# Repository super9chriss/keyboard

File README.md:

# custom keyboard
This is a split keyboard which can be aligned to work like a normal keyboard, it also has a removable numpad which conects to the main keyboard using pogo connectors. 
The keycaps are going to be 3d printed using these keycaps: https://www.printables.com/model/593307-low-profile-small-mx-keycaps-set/files

I wanted to make a split keyboard since my wrist hurt after typing for a long time, but im used to typing on a normal keyboard so i wanted to have this possiblity aswel,
i use a numpad for some programs so i also wanted to have that but since my desk is alway cluttered with stuff i wanted to have a keyboard which isnt too big so i made it removable.
## PCB and schematic
| **PCB Layout** | **Schematic** |
| :---: | :---: |
||
||
||
|| 
## BOM
|Description        |quantity              |price                 |link                                                                                                                                                                                                                                                                                  |
|-------------------|----------------------|----------------------|--------------------------------------------------------------------------------------------------------------------------------------------------------------------------------------------------------------------------------------------------------------------------------------|
|switches           |110                   |25.99 + 4.72(shipping)|https://nl.aliexpress.com/item/1005010167220637.html?spm=a2g0o.cart.0.0.14d561d7dqnSf7&mp=1&pdp_npi=6%40dis%21EUR%21EUR%2046.41%21EUR%2025.99%21%21EUR%2023.51%21%21%21%40211b813b17699617589272174ea3c6%2112000051388572877%21ct%21NL%217243002615%21%211%210%21&gatewayAdapt=glo2nld|
|Pico               |2                     |4.89                  |https://nl.aliexpress.com/item/1005006839247100.html?spm=a2g0o.cart.0.0.14d561d7dqnSf7&mp=1&pdp_npi=6%40dis%21EUR%21EUR%204.89%21EUR%204.89%21%21EUR%204.42%21%21%21%40211b813b17699617589272174ea3c6%2112000051567246192%21ct%21NL%217243002615%21%211%210%21&gatewayAdapt=glo2nld   |
|pogo connector 5pin|2                     |7.02                  |https://nl.aliexpress.com/item/1005006839247100.html?spm=a2g0o.cart.0.0.14d561d7dqnSf7&mp=1&pdp_npi=6%40dis%21EUR%21EUR%204.89%21EUR%204.89%21%21EUR%204.42%21%21%21%40211b813b17699617589272174ea3c6%2112000051567246192%21ct%21NL%217243002615%21%211%210%21&gatewayAdapt=glo2nld   |
|diodes             |110(need to order 200)|3.98                  |https://nl.aliexpress.com/item/1005005574663623.html?spm=a2g0o.cart.0.0.14d561d7dqnSf7&mp=1&pdp_npi=6%40dis%21EUR%21EUR%201.99%21EUR%201.99%21%21EUR%201.80%21%21%21%40211b813b17699617589272174ea3c6%2112000033607802196%21ct%21NL%217243002615%21%212%210%21&gatewayAdapt=glo2nld   |
|PCB                |1                     |41.14                 |https://cart.jlcpcb.com/shopcart/cart                                                                                                                                                                                                                                                 |
|LED               |1                     |0              |Self sourced                                                                                                                                                                                                                                               |
|                   |total in euro:        |87.74                 |aliexpress coupon saves 4 euro so 83.74                                                                                                                                                                                                                                               |
|                   |in usd                |100                   |                                                                                                                                                                                                                                                                                      |

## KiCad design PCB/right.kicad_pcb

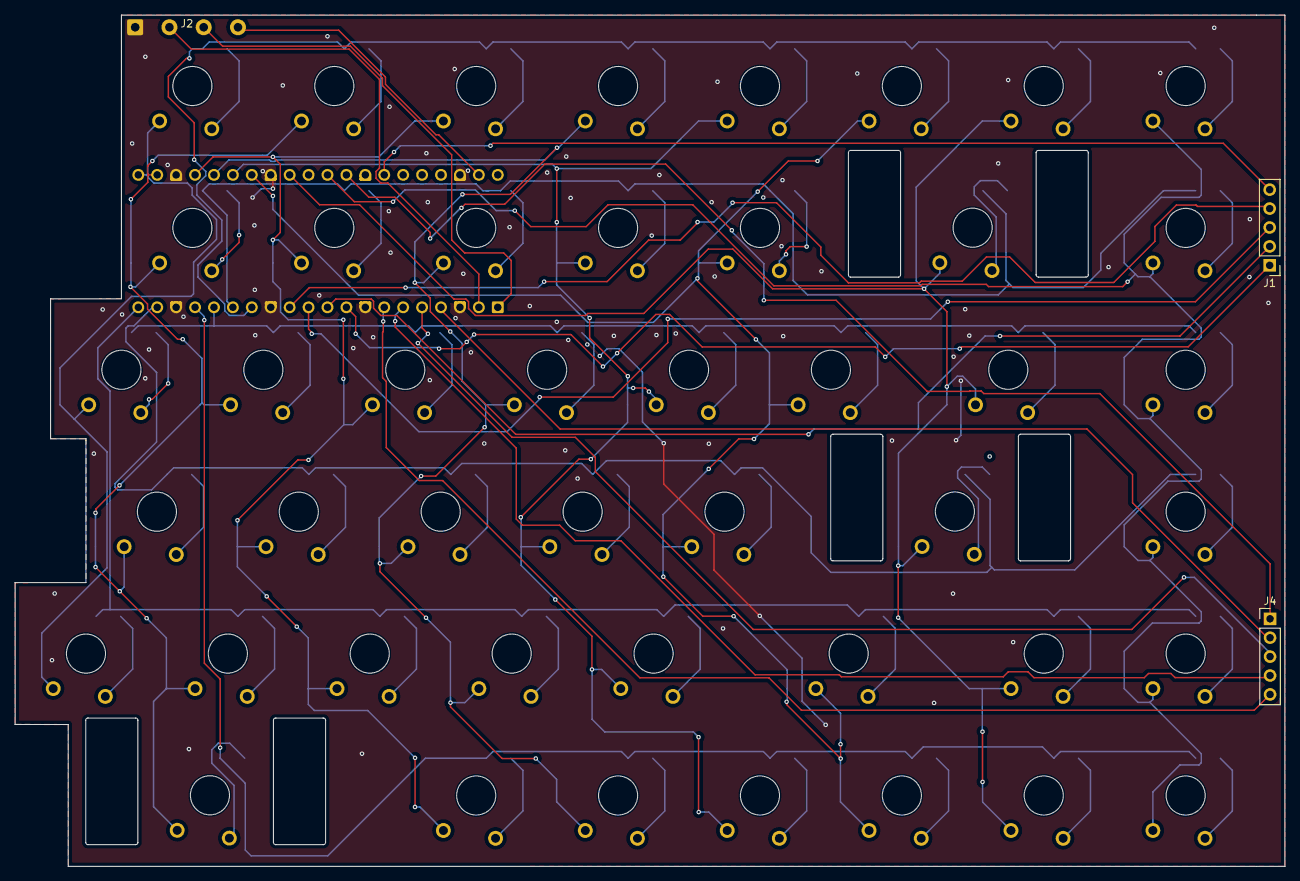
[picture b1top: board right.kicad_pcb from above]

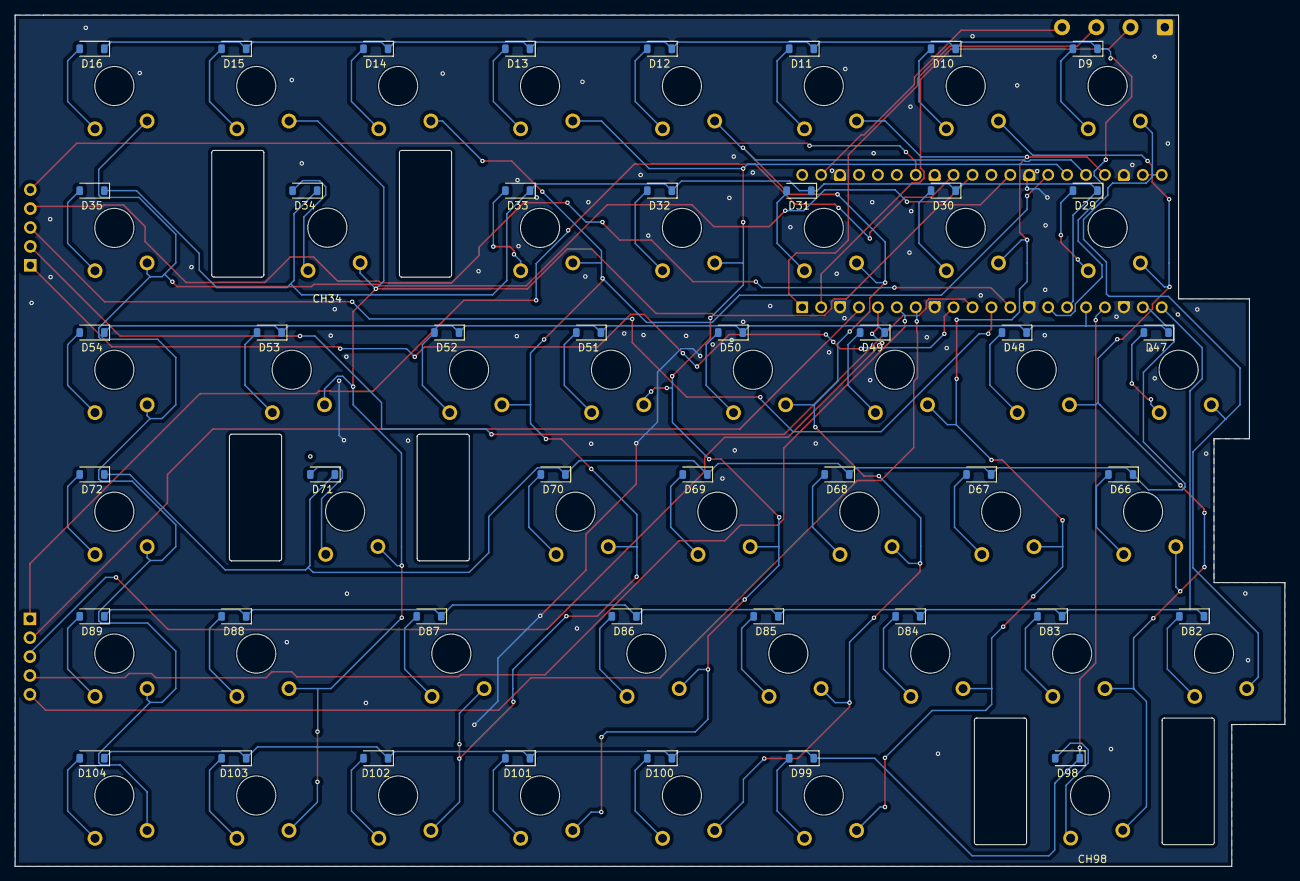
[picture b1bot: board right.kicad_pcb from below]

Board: 2 copper layers, 170.5 x 114.3 mm, 94 parts (46 on the bottom side), 73 nets.

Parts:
A1: RaspberryPi_Pico; RaspberryPi_Pico_Common_THT no silk only pins
CH9, CH10, CH11, CH12, CH13, CH14, CH15, CH16, CH29, CH30, CH31, CH32, CH33, CH35, CH47, CH48, CH49, CH50, CH51, CH52, CH53, CH54, CH66, CH67, CH68, CH69, CH70, CH72, CH82, CH83, CH84, CH85, CH86, CH87, CH88, CH89, CH99, CH100, CH101, CH102, CH103, CH104: KS33_SW_HS; SW_KS33_1u
CH34, CH71, CH98: KS33_SW_HS; Gateron_Low_Profile_Socket_Stabilizer_2U
D9, D10, D11, D12, D13, D14, D15, D16, D29, D30, D31, D32, D33, D34, D35, D47, D48, D49, D50, D51, D52, D53, D54, D66, D67, D68, D69, D70, D71, D72, D82, D83, D84, D85, D86, D87, D88, D89, D98, D99, D100, D101, D102, D103, D104: D; D_SOD-123
J1, J4: Conn_01x05_Socket; PinHeader_1x05_P2.54mm_Vertical
J2: Conn_01x04_Socket; SolderWire-0.5sqmm_1x04_P4.6mm_D0.9mm_OD2.1mm

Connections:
GND1: A1.3 (GND), A1.8 (GND), A1.13 (GND), A1.18 (GND), A1.23 (GND), A1.28 (GND), A1.38 (GND), J2.1
unnamed: A1.1 (GPIO0), J2.3
unnamed: A1.2 (GPIO1), J2.2
unnamed: A1.39 (VSYS), J2.4
unnamed: CH9.2, D9.2 (A)
unnamed: CH10.2, D10.2 (A)
unnamed: CH11.2, D11.2 (A)
unnamed: CH12.2, D12.2 (A)
unnamed: CH13.2, D13.2 (A)
unnamed: CH14.2, D14.2 (A)
unnamed: CH15.2, D15.2 (A)
unnamed: CH16.2, D16.2 (A)
unnamed: CH29.2, D29.2 (A)
unnamed: CH30.2, D30.2 (A)
unnamed: CH31.2, D31.2 (A)
unnamed: CH32.2, D32.2 (A)
unnamed: CH33.2, D33.2 (A)
unnamed: CH34.2, D34.2 (A)
unnamed: CH35.2, D35.2 (A)
unnamed: CH47.2, D47.2 (A)
unnamed: CH48.2, D48.2 (A)
unnamed: CH49.2, D49.2 (A)
unnamed: CH50.2, D50.2 (A)
unnamed: CH51.2, D51.2 (A)
unnamed: CH52.2, D52.2 (A)
unnamed: CH53.2, D53.2 (A)
unnamed: CH54.2, D54.2 (A)
unnamed: CH66.2, D66.2 (A)
unnamed: CH67.2, D67.2 (A)
unnamed: CH68.2, D68.2 (A)
unnamed: CH69.2, D69.2 (A)
unnamed: CH70.2, D70.2 (A)
unnamed: CH71.2, D71.2 (A)
unnamed: CH72.2, D72.2 (A)
unnamed: CH82.2, D82.2 (A)
unnamed: CH83.2, D83.2 (A)
unnamed: CH84.2, D84.2 (A)
unnamed: CH85.2, D85.2 (A)
unnamed: CH86.2, D86.2 (A)
unnamed: CH87.2, D87.2 (A)
unnamed: CH88.2, D88.2 (A)
unnamed: CH89.2, D89.2 (A)
unnamed: CH98.2, D98.2 (A)
unnamed: CH99.2, D99.2 (A)
unnamed: CH100.2, D100.2 (A)
unnamed: CH101.2, D101.2 (A)
unnamed: CH102.2, D102.2 (A)
unnamed: CH103.2, D103.2 (A)
unnamed: CH104.2, D104.2 (A)
col8: A1.21 (GPIO16), CH9.1, CH47.1, CH82.1
col9: A1.22 (GPIO17), CH10.1, CH29.1, CH48.1, CH66.1, CH83.1, CH98.1
col10: A1.24 (GPIO18), CH11.1, CH30.1, CH49.1, CH67.1, CH84.1, CH99.1
col11: A1.25 (GPIO19), CH12.1, CH31.1, CH50.1, CH68.1, CH85.1, CH100.1
col12: A1.26 (GPIO20), CH13.1, CH32.1, CH51.1, CH69.1, CH86.1, CH101.1
col13: A1.27 (GPIO21), CH14.1, CH33.1, CH52.1, CH70.1, CH87.1, CH102.1
col14: A1.29 (GPIO22), CH15.1, CH34.1, CH53.1, CH71.1, CH88.1, CH103.1
col15: A1.31 (GPIO26_ADC0), CH16.1, CH35.1, CH54.1, CH72.1, CH89.1, CH104.1
col16: A1.12 (GPIO9), J1.4
col17: A1.11 (GPIO8), J1.3
col18: A1.10 (GPIO7), J1.2
col19: A1.9 (GPIO6), J1.1
row6: A1.14 (GPIO10), D9.1 (K), D10.1 (K), D11.1 (K), D12.1 (K), D13.1 (K), D14.1 (K), D15.1 (K), D16.1 (K)
row7: A1.15 (GPIO11), D29.1 (K), D30.1 (K), D31.1 (K), D32.1 (K), D33.1 (K), D34.1 (K), D35.1 (K)
row8: A1.16 (GPIO12), D47.1 (K), D48.1 (K), D49.1 (K), D50.1 (K), D51.1 (K), D52.1 (K), D53.1 (K), D54.1 (K)
row9: A1.19 (GPIO14), D66.1 (K), D67.1 (K), D68.1 (K), D69.1 (K), D70.1 (K), D71.1 (K), D72.1 (K)
row10: A1.20 (GPIO15), D82.1 (K), D83.1 (K), D84.1 (K), D85.1 (K), D86.1 (K), D87.1 (K), D88.1 (K), D89.1 (K)
row11: A1.17 (GPIO13), D98.1 (K), D99.1 (K), D100.1 (K), D101.1 (K), D102.1 (K), D103.1 (K), D104.1 (K)
row12: A1.34 (GPIO28_ADC2), J1.5
row13: A1.32 (GPIO27_ADC1), J4.1
row14: A1.4 (GPIO2), J4.2
row15: A1.5 (GPIO3), J4.3
row16: A1.6 (GPIO4), J4.4
row17: A1.7 (GPIO5), J4.5

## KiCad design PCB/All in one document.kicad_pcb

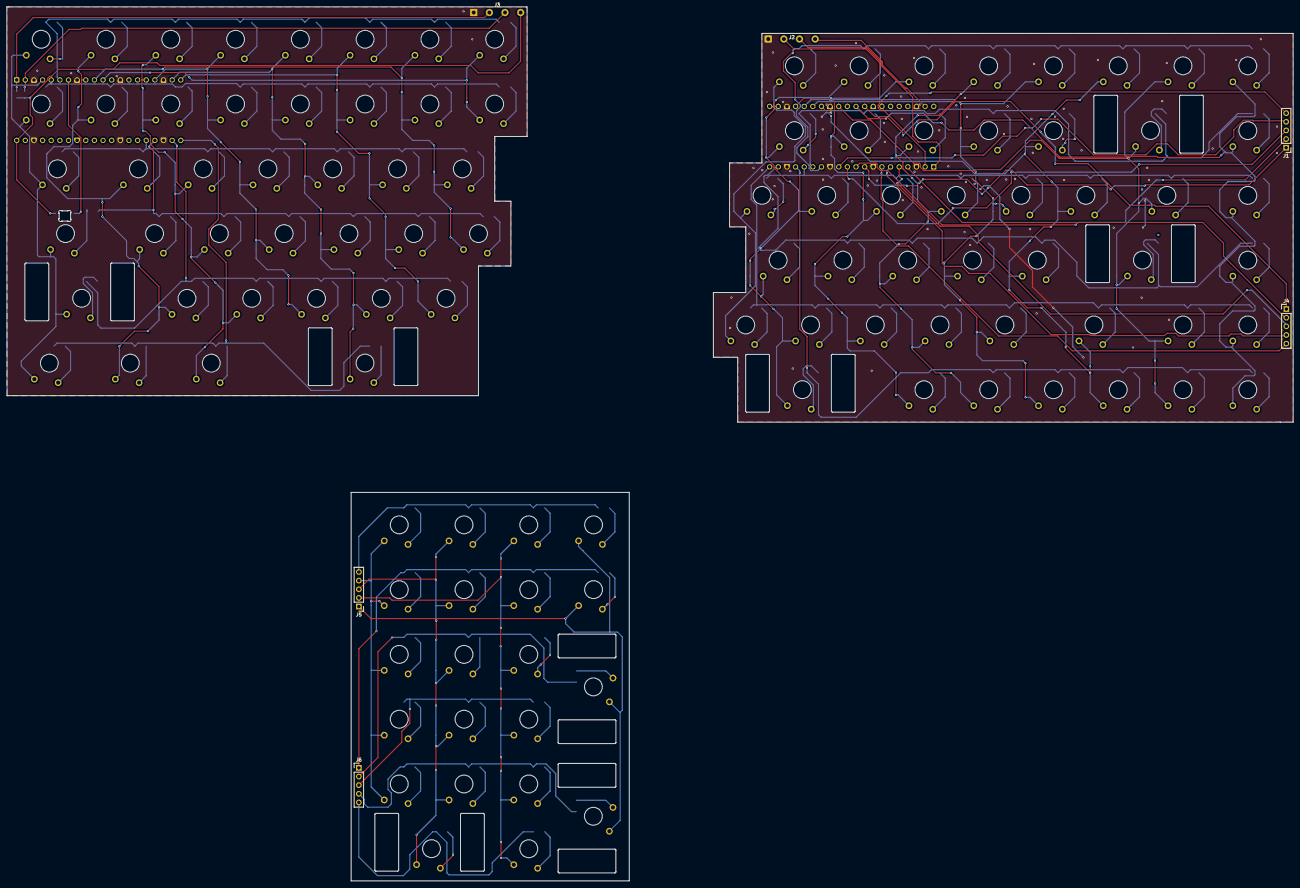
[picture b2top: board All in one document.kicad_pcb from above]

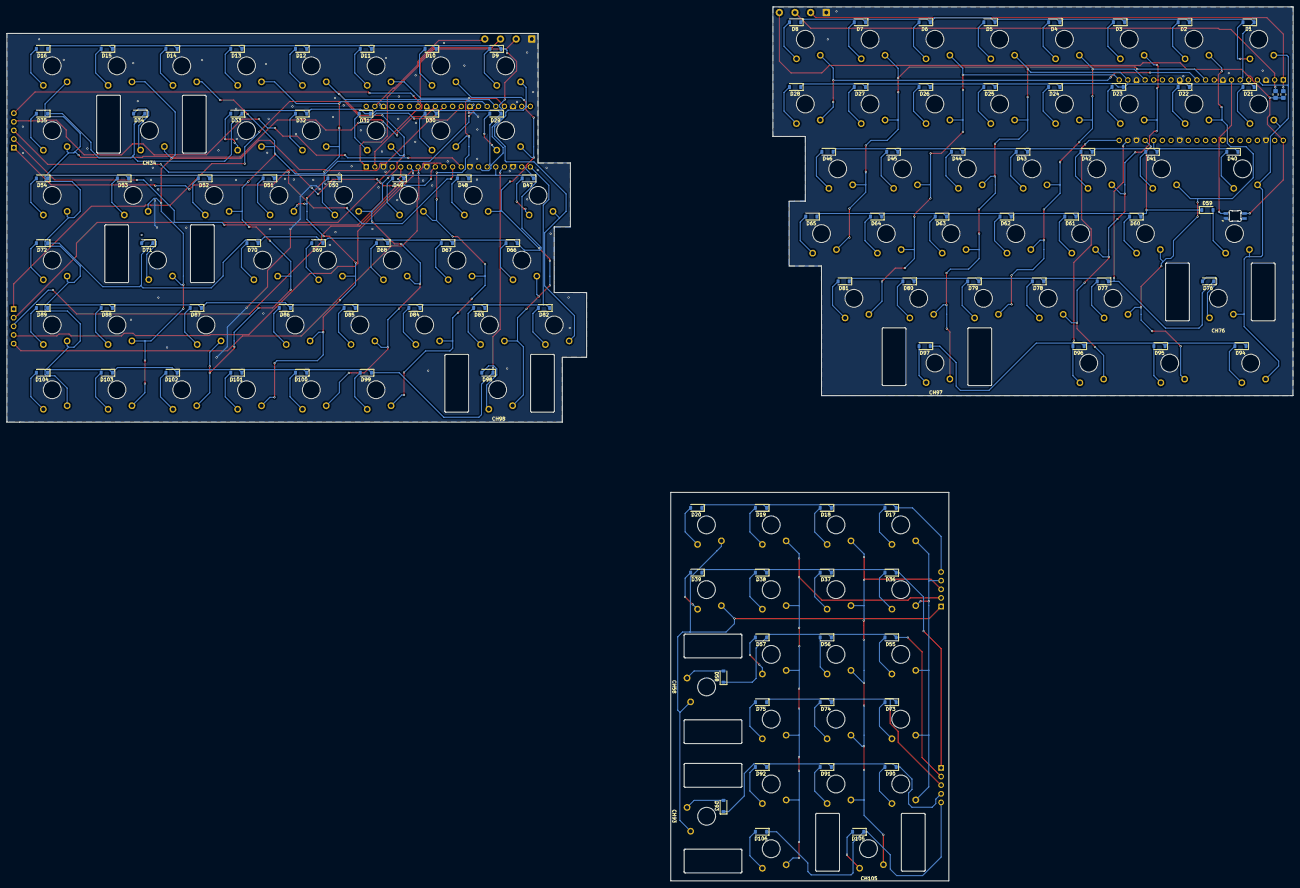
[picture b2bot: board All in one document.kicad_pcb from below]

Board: 2 copper layers, 378.3 x 257.0 mm, 223 parts (111 on the bottom side), 163 nets.

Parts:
A1, A2: RaspberryPi_Pico; RaspberryPi_Pico_Common_THT no silk only pins
CH1, CH2, CH3, CH4, CH5, CH6, CH7, CH8, CH9, CH10, CH11, CH12, CH13, CH14, CH15, CH16, CH17, CH18, CH19, CH20, CH21, CH22, CH23, CH24, CH25, CH26, CH27, CH28, CH29, CH30, CH31, CH32, CH33, CH35, CH36, CH37, CH38, CH39, CH40, CH41, CH42, CH43, CH44, CH45, CH46, CH47, CH48, CH49, CH50, CH51, CH52, CH53, CH54, CH55, CH56, CH57, CH59, CH60, CH61, CH62, CH63, CH64, CH65, CH66, CH67, CH68, CH69, CH70, CH72, CH73, CH74, CH75, CH77, CH78, CH79, CH80, CH81, CH82, CH83, CH84, CH85, CH86, CH87, CH88, CH89, CH90, CH91, CH92, CH94, CH95, CH96, CH99, CH100, CH101, CH102, CH103, CH104, CH106: KS33_SW_HS; SW_KS33_1u
CH34, CH58, CH71, CH76, CH93, CH97, CH98, CH105: KS33_SW_HS; Gateron_Low_Profile_Socket_Stabilizer_2U
D1, D2, D3, D4, D5, D6, D7, D8, D9, D10, D11, D12, D13, D14, D15, D16, D17, D18, D19, D20, D21, D22, D23, D24, D25, D26, D27, D28, D29, D30, D31, D32, D33, D34, D35, D36, D37, D38, D39, D40, D41, D42, D43, D44, D45, D46, D47, D48, D49, D50, D51, D52, D53, D54, D55, D56, D57, D58, D59, D60, D61, D62, D63, D64, D65, D66, D67, D68, D69, D70, D71, D72, D73, D74, D75, D76, D77, D78, D79, D80, D81, D82, D83, D84, D85, D86, D87, D88, D89, D90, D91, D92, D93, D94, D95, D96, D97, D98, D99, D100, D101, D102, D103, D104, D105, D106: D; D_SOD-123
J1, J4, J5, J6: Conn_01x05_Socket; PinHeader_1x05_P2.54mm_Vertical
J2, J3: Conn_01x04_Socket; SolderWire-0.5sqmm_1x04_P4.6mm_D0.9mm_OD2.1mm
LED1: SK6812MINI-E; LED_6028R
R1, R2: 4.7K; R_0805_2012Metric_Pad1.20x1.40mm_HandSolder

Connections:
GND1: A1.3 (GND), A1.8 (GND), A1.13 (GND), A1.18 (GND), A1.23 (GND), A1.28 (GND), A1.38 (GND), J2.1
GND2: A2.3 (GND), A2.8 (GND), A2.13 (GND), A2.18 (GND), A2.23 (GND), A2.28 (GND), A2.38 (GND), J3.1, LED1.4 (VSS)
unnamed: A1.1 (GPIO0), J2.3
unnamed: A1.2 (GPIO1), J2.2
unnamed: A1.39 (VSYS), J2.4
unnamed: A2.1 (GPIO0), J3.2, R1.2
unnamed: A2.2 (GPIO1), J3.3, R2.2
unnamed: A2.7 (GPIO5), LED1.3 (DIN)
unnamed: A2.40 (VBUS), J3.4, LED1.1 (VDD), R1.1, R2.1
unnamed: CH1.2, D1.2 (A)
unnamed: CH2.2, D2.2 (A)
unnamed: CH3.2, D3.2 (A)
unnamed: CH4.2, D4.2 (A)
unnamed: CH5.2, D5.2 (A)
unnamed: CH6.2, D6.2 (A)
unnamed: CH7.2, D7.2 (A)
unnamed: CH8.2, D8.2 (A)
unnamed: CH9.2, D9.2 (A)
unnamed: CH10.2, D10.2 (A)
unnamed: CH11.2, D11.2 (A)
unnamed: CH12.2, D12.2 (A)
unnamed: CH13.2, D13.2 (A)
unnamed: CH14.2, D14.2 (A)
unnamed: CH15.2, D15.2 (A)
unnamed: CH16.2, D16.2 (A)
unnamed: CH17.2, D17.2 (A)
unnamed: CH18.2, D18.2 (A)
unnamed: CH19.2, D19.2 (A)
unnamed: CH20.2, D20.2 (A)
unnamed: CH21.2, D21.2 (A)
unnamed: CH22.2, D22.2 (A)
unnamed: CH23.2, D23.2 (A)
unnamed: CH24.2, D24.2 (A)
unnamed: CH25.2, D25.2 (A)
unnamed: CH26.2, D26.2 (A)
unnamed: CH27.2, D27.2 (A)
unnamed: CH28.2, D28.2 (A)
unnamed: CH29.2, D29.2 (A)
unnamed: CH30.2, D30.2 (A)
unnamed: CH31.2, D31.2 (A)
unnamed: CH32.2, D32.2 (A)
unnamed: CH33.2, D33.2 (A)
unnamed: CH34.2, D34.2 (A)
unnamed: CH35.2, D35.2 (A)
unnamed: CH36.2, D36.2 (A)
unnamed: CH37.2, D37.2 (A)
unnamed: CH38.2, D38.2 (A)
unnamed: CH39.2, D39.2 (A)
unnamed: CH40.2, D40.2 (A)
unnamed: CH41.2, D41.2 (A)
unnamed: CH42.2, D42.2 (A)
unnamed: CH43.2, D43.2 (A)
unnamed: CH44.2, D44.2 (A)
unnamed: CH45.2, D45.2 (A)
unnamed: CH46.2, D46.2 (A)
unnamed: CH47.2, D47.2 (A)
unnamed: CH48.2, D48.2 (A)
unnamed: CH49.2, D49.2 (A)
unnamed: CH50.2, D50.2 (A)
unnamed: CH51.2, D51.2 (A)
unnamed: CH52.2, D52.2 (A)
unnamed: CH53.2, D53.2 (A)
unnamed: CH54.2, D54.2 (A)
unnamed: CH55.2, D55.2 (A)
unnamed: CH56.2, D56.2 (A)
unnamed: CH57.2, D57.2 (A)
unnamed: CH58.2, D58.2 (A)
unnamed: CH59.2, D59.2 (A)
unnamed: CH60.2, D60.2 (A)
unnamed: CH61.2, D61.2 (A)
unnamed: CH62.2, D62.2 (A)
unnamed: CH63.2, D63.2 (A)
unnamed: CH64.2, D64.2 (A)
unnamed: CH65.2, D65.2 (A)
unnamed: CH66.2, D66.2 (A)
unnamed: CH67.2, D67.2 (A)
unnamed: CH68.2, D68.2 (A)
unnamed: CH69.2, D69.2 (A)
unnamed: CH70.2, D70.2 (A)
unnamed: CH71.2, D71.2 (A)
unnamed: CH72.2, D72.2 (A)
unnamed: CH73.2, D73.2 (A)
unnamed: CH74.2, D74.2 (A)
unnamed: CH75.2, D75.2 (A)
unnamed: CH76.2, D76.2 (A)
unnamed: CH77.2, D77.2 (A)
unnamed: CH78.2, D78.2 (A)
unnamed: CH79.2, D79.2 (A)
unnamed: CH80.2, D80.2 (A)
unnamed: CH81.2, D81.2 (A)
unnamed: CH82.2, D82.2 (A)
unnamed: CH83.2, D83.2 (A)
unnamed: CH84.2, D84.2 (A)
unnamed: CH85.2, D85.2 (A)
unnamed: CH86.2, D86.2 (A)
unnamed: CH87.2, D87.2 (A)
unnamed: CH88.2, D88.2 (A)
unnamed: CH89.2, D89.2 (A)
unnamed: CH90.2, D90.2 (A)
unnamed: CH91.2, D91.2 (A)
unnamed: CH92.2, D92.2 (A)
unnamed: CH93.2, D93.2 (A)
unnamed: CH94.2, D94.2 (A)
unnamed: CH95.2, D95.2 (A)
unnamed: CH96.2, D96.2 (A)
unnamed: CH97.2, D97.2 (A)
unnamed: CH98.2, D98.2 (A)
unnamed: CH99.2, D99.2 (A)
unnamed: CH100.2, D100.2 (A)
unnamed: CH101.2, D101.2 (A)
unnamed: CH102.2, D102.2 (A)
unnamed: CH103.2, D103.2 (A)
unnamed: CH104.2, D104.2 (A)
unnamed: CH105.2, D105.2 (A)
unnamed: CH106.2, D106.2 (A)
col0: A2.4 (GPIO2), CH1.1, CH21.1, CH40.1, CH59.1, CH76.1, CH94.1
col1: A2.9 (GPIO6), CH2.1, CH22.1, CH41.1, CH60.1, CH77.1, CH95.1
col2: A2.16 (GPIO12), CH3.1, CH23.1, CH42.1, CH61.1, CH78.1, CH96.1
col3: A2.17 (GPIO13), CH4.1, CH24.1, CH43.1, CH62.1, CH79.1
col4: A2.19 (GPIO14), CH5.1, CH25.1, CH44.1, CH63.1, CH80.1, CH97.1
col5: A2.20 (GPIO15), CH6.1, CH26.1, CH45.1, CH64.1, CH81.1
col6: A2.10 (GPIO7), CH7.1, CH27.1, CH46.1, CH65.1
col7: A2.11 (GPIO8), CH8.1, CH28.1
col8: A1.21 (GPIO16), CH9.1, CH47.1, CH82.1
col9: A1.22 (GPIO17), CH10.1, CH29.1, CH48.1, CH66.1, CH83.1, CH98.1
col10: A1.24 (GPIO18), CH11.1, CH30.1, CH49.1, CH67.1, CH84.1, CH99.1
col11: A1.25 (GPIO19), CH12.1, CH31.1, CH50.1, CH68.1, CH85.1, CH100.1
col12: A1.26 (GPIO20), CH13.1, CH32.1, CH51.1, CH69.1, CH86.1, CH101.1
col13: A1.27 (GPIO21), CH14.1, CH33.1, CH52.1, CH70.1, CH87.1, CH102.1
col14: A1.29 (GPIO22), CH15.1, CH34.1, CH53.1, CH71.1, CH88.1, CH103.1
col15: A1.31 (GPIO26_ADC0), CH16.1, CH35.1, CH54.1, CH72.1, CH89.1, CH104.1
col16: A1.12 (GPIO9), J1.4
col16N: CH17.1, CH36.1, CH55.1, CH73.1, CH90.1, J5.4
col17: A1.11 (GPIO8), J1.3
col17N: CH18.1, CH37.1, CH56.1, CH74.1, CH91.1, CH105.1, J5.3
col18: A1.10 (GPIO7), J1.2
col18N: CH19.1, CH38.1, CH57.1, CH75.1, CH92.1, CH106.1, J5.2
col19: A1.9 (GPIO6), J1.1
col19N: CH20.1, CH39.1, CH58.1, CH93.1, J5.1
row0: A2.6 (GPIO4), D1.1 (K), D2.1 (K), D3.1 (K), D4.1 (K), D5.1 (K), D6.1 (K), D7.1 (K), D8.1 (K)
row1: A2.5 (GPIO3), D21.1 (K), D22.1 (K), D23.1 (K), D24.1 (K), D25.1 (K), D26.1 (K), D27.1 (K), D28.1 (K)
row2: A2.25 (GPIO19), D40.1 (K), D41.1 (K), D42.1 (K), D43.1 (K), D44.1 (K), D45.1 (K), D46.1 (K)
row3: A2.24 (GPIO18), D59.1 (K), D60.1 (K), D61.1 (K), D62.1 (K), D63.1 (K), D64.1 (K), D65.1 (K)
row4: A2.22 (GPIO17), D76.1 (K), D77.1 (K), D78.1 (K), D79.1 (K), D80.1 (K), D81.1 (K)
row5: A2.21 (GPIO16), D94.1 (K), D95.1 (K), D96.1 (K), D97.1 (K)
row6: A1.14 (GPIO10), D9.1 (K), D10.1 (K), D11.1 (K), D12.1 (K), D13.1 (K), D14.1 (K), D15.1 (K), D16.1 (K)
row7: A1.15 (GPIO11), D29.1 (K), D30.1 (K), D31.1 (K), D32.1 (K), D33.1 (K), D34.1 (K), D35.1 (K)
row8: A1.16 (GPIO12), D47.1 (K), D48.1 (K), D49.1 (K), D50.1 (K), D51.1 (K), D52.1 (K), D53.1 (K), D54.1 (K)
row9: A1.19 (GPIO14), D66.1 (K), D67.1 (K), D68.1 (K), D69.1 (K), D70.1 (K), D71.1 (K), D72.1 (K)
row10: A1.20 (GPIO15), D82.1 (K), D83.1 (K), D84.1 (K), D85.1 (K), D86.1 (K), D87.1 (K), D88.1 (K), D89.1 (K)
row11: A1.17 (GPIO13), D98.1 (K), D99.1 (K), D100.1 (K), D101.1 (K), D102.1 (K), D103.1 (K), D104.1 (K)
row12: A1.34 (GPIO28_ADC2), J1.5
row12N: D17.1 (K), D18.1 (K), D19.1 (K), D20.1 (K), J5.5
row13: A1.32 (GPIO27_ADC1), J4.1
row13N: D36.1 (K), D37.1 (K), D38.1 (K), D39.1 (K), J6.1
row14: A1.4 (GPIO2), J4.2
row14N: D55.1 (K), D56.1 (K), D57.1 (K), D58.1 (K), J6.2
row15: A1.5 (GPIO3), J4.3
row15N: D73.1 (K), D74.1 (K), D75.1 (K), J6.3
row16: A1.6 (GPIO4), J4.4
row16N: D90.1 (K), D91.1 (K), D92.1 (K), D93.1 (K), J6.4
row17: A1.7 (GPIO5), J4.5
row17N: D105.1 (K), D106.1 (K), J6.5

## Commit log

2026-02-01 initial
2026-02-01 second
2026-02-01 third
2026-02-12 upload
2026-02-13 added keycaps to 3d model
2026-02-17 added Keycap files in step
